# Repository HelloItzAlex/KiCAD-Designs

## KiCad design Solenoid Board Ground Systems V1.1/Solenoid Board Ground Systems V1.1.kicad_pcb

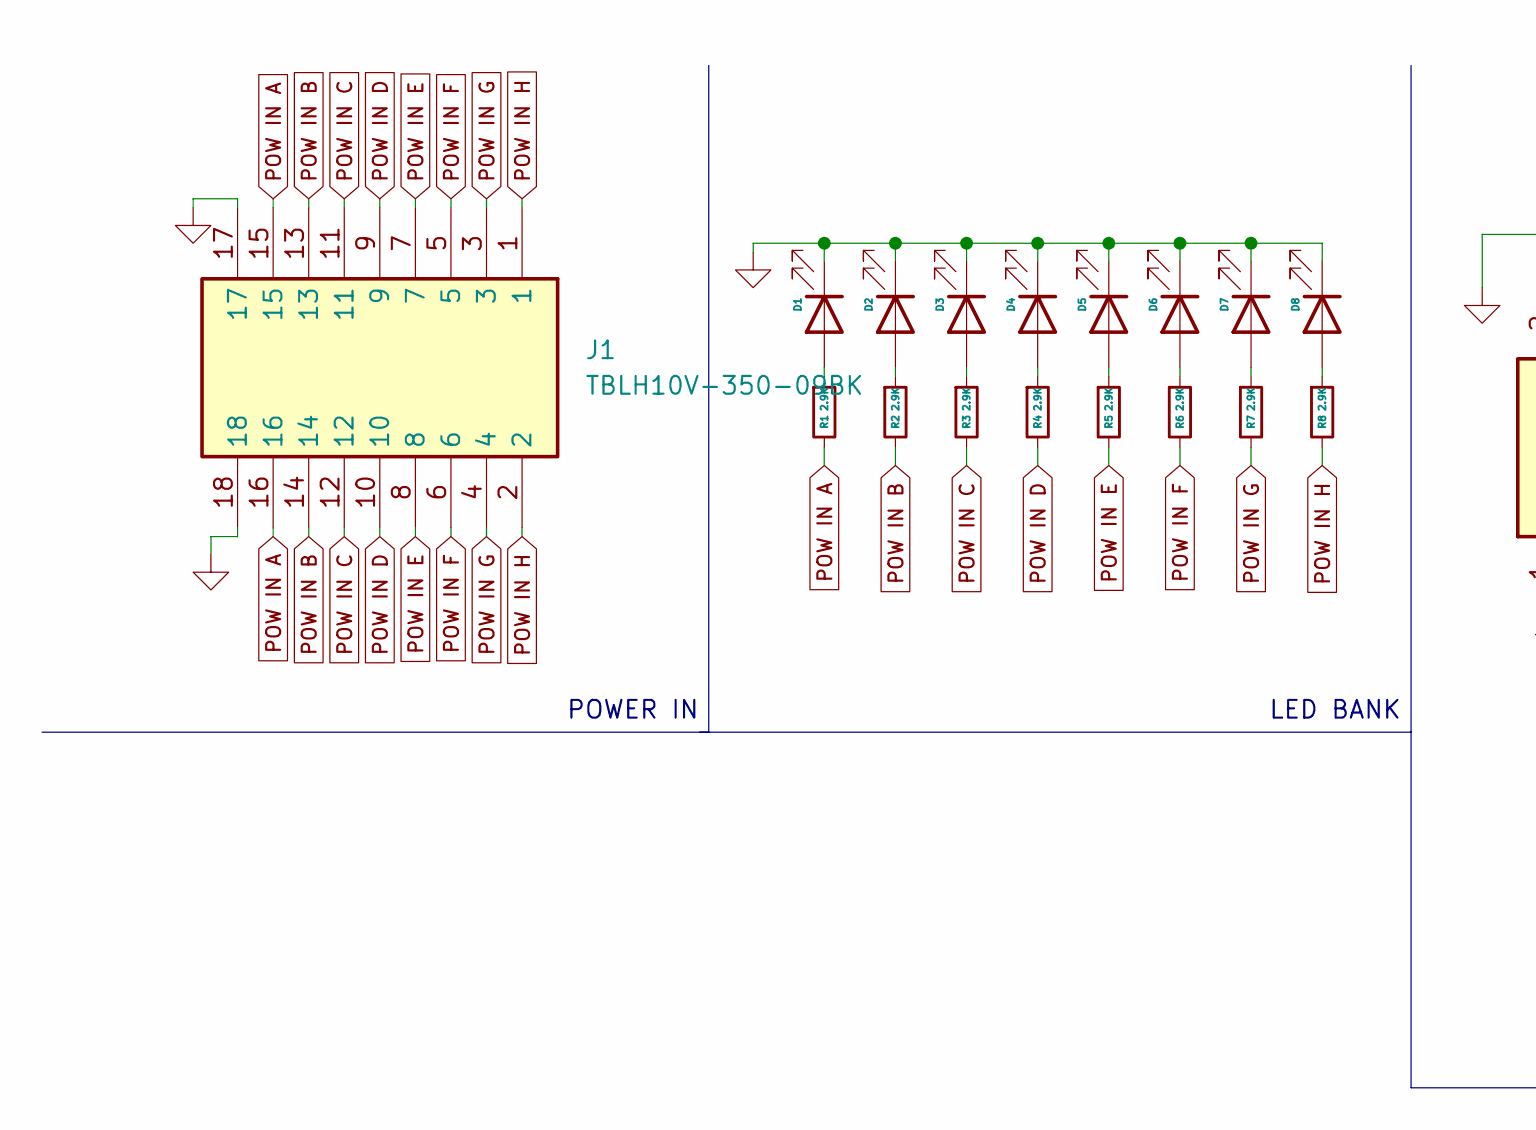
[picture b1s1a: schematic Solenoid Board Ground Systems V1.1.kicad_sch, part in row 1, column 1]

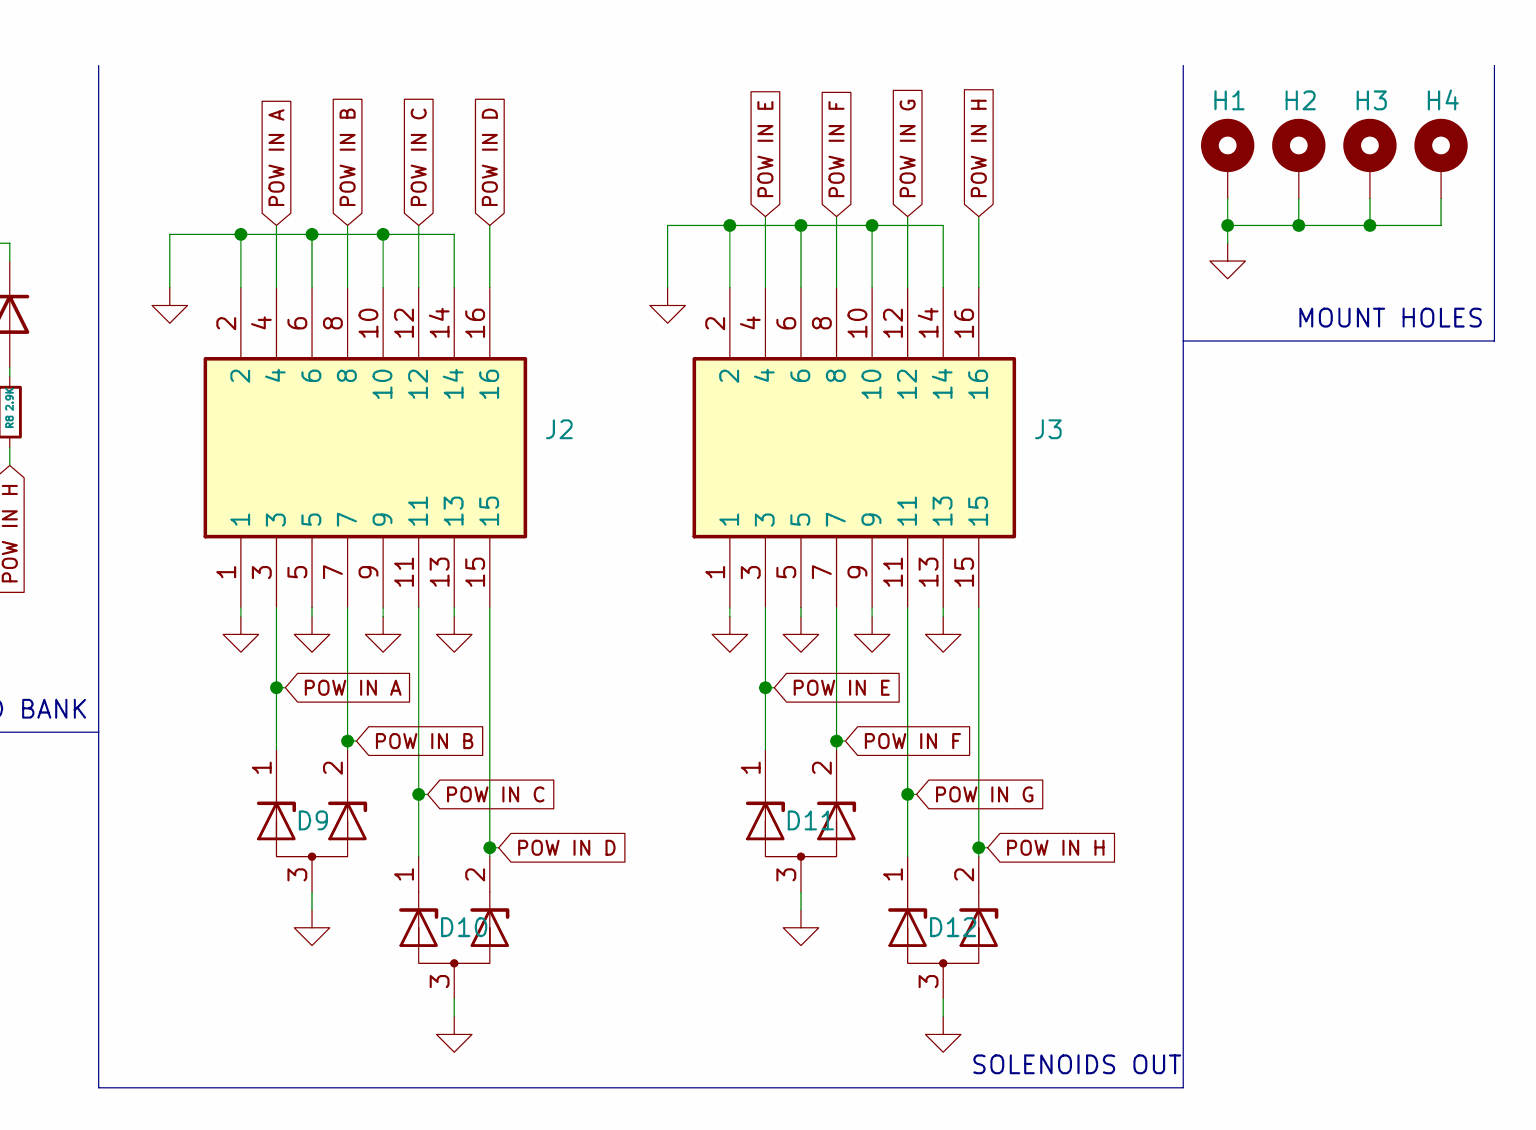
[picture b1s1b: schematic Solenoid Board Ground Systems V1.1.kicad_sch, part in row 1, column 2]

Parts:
D1, D2, D3, D4, D5, D6, D7, D8: LED; LED_0805_2012Metric
D9, D10, D11, D12: MMBZxx; SOT-23
H1, H2, H3, H4: MountingHole_Pad; MountingHole_3.2mm_M3_DIN965_Pad_TopBottom
J1: TBLH10V-350-09BK; RHDR18W80P550X350_2X9_3220X850X1420P; Mouser Part Number 490-TBLH10V-350-09BK
J2, J3: TBLH10V-350-08BK; RHDR16W80P550X350_2X8_2870X850X1420P; Mouser Part Number 490-TBLH10V-350-08BK
R1, R2, R3, R4, R5, R6, R7, R8: 2.9K; R_0603_1608Metric

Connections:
GND: D1.1 (K), D2.1 (K), D3.1 (K), D4.1 (K), D5.1 (K), D6.1 (K), D7.1 (K), D8.1 (K), D9.3 (A), D10.3 (A), D11.3 (A), D12.3 (A), H1.1, H2.1, H3.1, H4.1, J1.17, J1.18, J2.1, J2.2, J2.5, J2.6, J2.9, J2.10, J2.13, J2.14, J3.1, J3.2, J3.5, J3.6, J3.9, J3.10, J3.13, J3.14
unnamed: D1.2 (A), R1.1
unnamed: D2.2 (A), R2.1
unnamed: D3.2 (A), R3.1
unnamed: D4.2 (A), R4.1
unnamed: D5.2 (A), R5.1
unnamed: D6.2 (A), R6.1
unnamed: D7.2 (A), R7.1
unnamed: D8.2 (A), R8.1
POW IN A: D9.1 (K), J1.15, J1.16, J2.3, J2.4, R1.2
POW IN B: D9.2 (K), J1.13, J1.14, J2.7, J2.8, R2.2
POW IN C: D10.1 (K), J1.11, J1.12, J2.11, J2.12, R3.2
POW IN D: D10.2 (K), J1.9, J1.10, J2.15, J2.16, R4.2
POW IN E: D11.1 (K), J1.7, J1.8, J3.3, J3.4, R5.2
POW IN F: D11.2 (K), J1.5, J1.6, J3.7, J3.8, R6.2
POW IN G: D12.1 (K), J1.3, J1.4, J3.11, J3.12, R7.2
POW IN H: D12.2 (K), J1.1, J1.2, J3.15, J3.16, R8.2

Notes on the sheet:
POWER IN
SOLENOIDS OUT
MOUNT HOLES
LED BANK

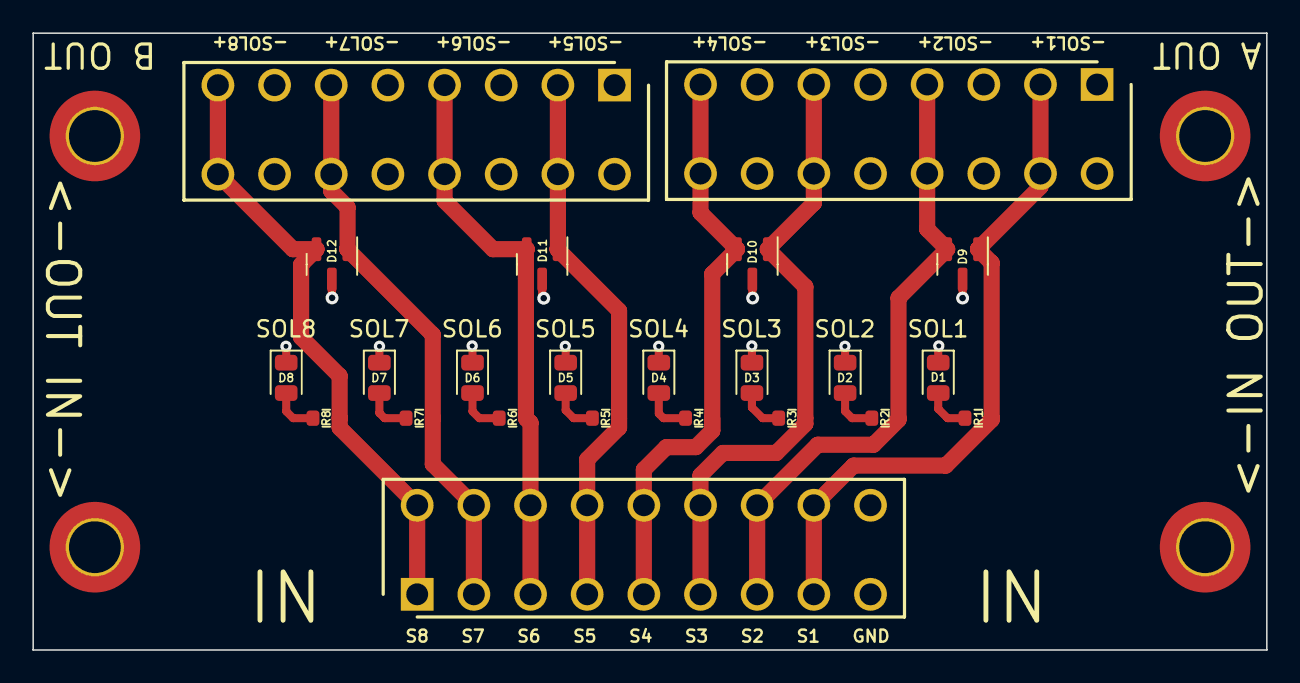
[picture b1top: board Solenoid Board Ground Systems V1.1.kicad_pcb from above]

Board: 2 copper layers, 76.2 x 38.1 mm, 27 parts (0 on the bottom side), 17 nets.

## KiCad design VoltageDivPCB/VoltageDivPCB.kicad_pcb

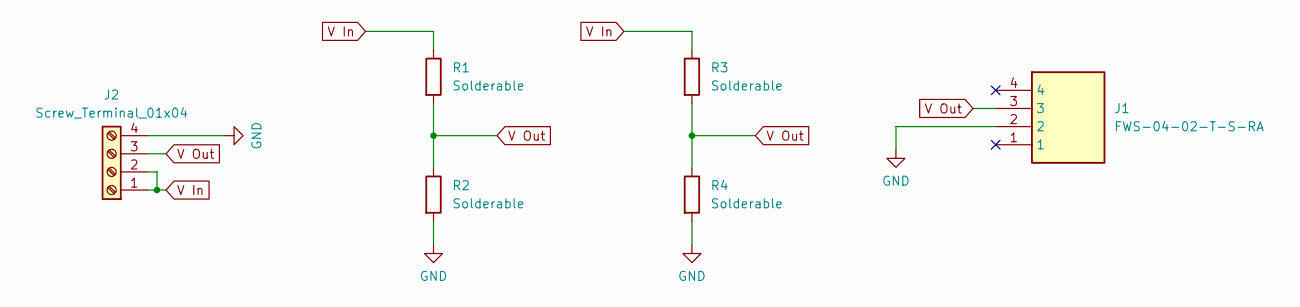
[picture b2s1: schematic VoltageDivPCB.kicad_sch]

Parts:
J1: FWS-04-02-T-S-RA; FWS0402TSRA; Mouser Part Number 200-FWS0402TSRA
J2: Screw_Terminal_01x04; TerminalBlock_Phoenix_PT-1,5-4-3.5-H_1x04_P3.50mm_Horizontal
R1, R2: Solderable; R_Axial_DIN0204_L3.6mm_D1.6mm_P5.08mm_Horizontal
R3, R4: Solderable; R_0603_1608Metric_Pad0.98x0.95mm_HandSolder

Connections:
GND: J1.2, J2.4, R2.2, R4.2
V In: J2.1, J2.2, R1.1, R3.1
V Out: J1.3, J2.3, R1.2, R2.1, R3.2, R4.1

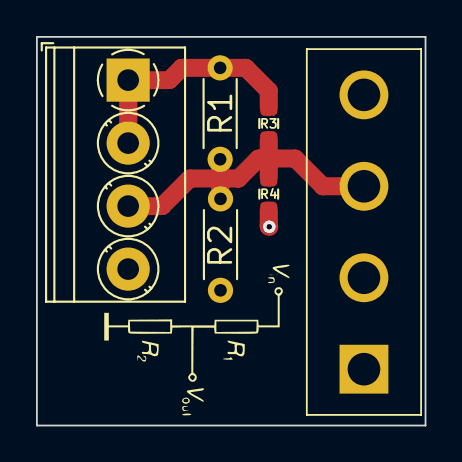
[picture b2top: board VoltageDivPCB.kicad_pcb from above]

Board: 2 copper layers, 21.6 x 21.6 mm, 6 parts (0 on the bottom side), 3 nets.
